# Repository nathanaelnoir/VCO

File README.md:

# AHS VCO `main_clean`

This README describes the behavior of `main_clean/main/main.ino` in musical and mathematical terms. The sketch is a three-mode Mozzi oscillator for Arduino Nano with:

- 2-operator FM mode
- chord oscillator-bank mode
- additive oscillator-bank mode

The firmware runs Mozzi in 2-pin PWM output mode with a control rate of 128 Hz. Audio generation happens in `updateAudio()`, while potentiometers, CV inputs, mode switching, oscillator frequencies, and table selections are updated in `updateControl()`.

## Inputs And Modes

The sketch reads these analog inputs:

| Name in code | Analog input | Main purpose |
| --- | ---: | --- |
| `AnalogRead0` | A0 | base pitch knob |
| `AnalogRead1` | A1 | mode-dependent parameter 1 |
| `Mode_CV` | A2 | mode CV selection |
| `AnalogRead3` | A3 | mode-dependent parameter 2 |
| `AnalogRead4` | A4 | CV for parameter 1 |
| `AnalogRead5` | A5 | CV for parameter 2 |
| `Gain_CV_*` | A6 | output level CV |
| `AnalogRead7` | A7 | V/oct input |

There are three synthesis modes:

```cpp
kModeFm       = 0
kModeChord    = 1
kModeAdditive = 2
```

The physical mode switch chooses a base ordering, and the mode CV chooses one of the three modes inside that ordering. Mathematically, the result is a discrete selector:

$$
M \in \{\mathrm{FM}, \mathrm{Chord}, \mathrm{Additive}\}
$$

where `Mode_CV` is computed by mapping the mode CV ADC value into:

$$
\mathrm{ModeCV} = \left\lfloor \mathrm{map}(A_2, 0, 1023, 0, 2) \right\rfloor
$$

The switch then permutes the three possible modes.

## Pitch Model

The sketch uses a lookup table called `voctpow`. It stores values from roughly `0` to `4.995`, indexed by the V/oct ADC input. The frequency logic repeatedly uses:

$$
f = f_\mathrm{base} \cdot 2^{V}
$$

where:

$$
V = \mathrm{voctpow}[\mathrm{ADC}]
$$

So the table is effectively a quantized exponential pitch control. If the V/oct ADC index increases by about one octave worth of table distance, the frequency doubles.

The helper:

```cpp
readVoctPow(index)
```

constrains the index to `0...1023`, then reads the floating-point value from program memory. This protects table access when chord offsets and inversion offsets are added.

## Output Level

The level CV is mapped to `0...255`:

$$
G = \mathrm{map}(A_6, 0, 1023, 0, 255)
$$

Audio samples are usually multiplied by:

$$
\frac{G}{256}
$$

Then the result is clipped to the signed 8-bit audio range:

$$
y = \mathrm{clip}(x, -128, 127)
$$

This is what `clipAudio8()` does.

## Wavetable Oscillators

The sketch uses Mozzi `Oscil` objects. Conceptually, each oscillator reads periodically through a table:

$$
x[n] = T(\phi[n])
$$

with phase:

$$
\phi[n+1] = \phi[n] + \Delta \phi
$$

where the phase increment is proportional to frequency:

$$
\Delta \phi \propto \frac{f}{f_s}
$$

Different tables give different waveforms:

| Wave enum | Table |
| --- | --- |
| `kWaveSaw` | saw |
| `kWaveSquare` | square |
| `kWaveTriangle` | triangle |
| `kWaveSine` | sine |
| `kWaveChebyshev` | Chebyshev waveshape |
| `kWaveHalfSine` | half sine |
| `kWaveSigmoid` | sigmoid waveshape |
| `kWavePhasor` | phasor |

## FM / 2-Operator Mode

FM mode uses one carrier oscillator and one modulator oscillator. In `main_clean`, both are cosine-table oscillators:

```cpp
aCarrier(COS2048_DATA)
aModulator(COS2048_DATA)
```

The base carrier frequency is computed from the pitch knob and V/oct input:

$$
f_c = (2270658 + 5000A_0) \cdot 2^V
$$

This value is a fixed-point Mozzi frequency value, not a simple Hz value. The important musical idea is:

- `A0` raises the base carrier frequency
- V/oct multiplies the frequency exponentially

The modulator frequency is derived from the carrier frequency and parameter 1:

$$
f_m \propto f_c \cdot \left(\frac{A_1}{2} + \frac{A_4}{2}\right)
$$

In code:

```cpp
mod_freq = ((carrier_freq >> 8) * (A1 / 2 + A4 / 2));
```

So parameter 1 and its CV act like a modulation-ratio or modulation-frequency control. It is not a clean integer ratio knob; it is a broad digital scaling of the carrier frequency.

The phase deviation is computed from the modulator frequency and parameter 2:

$$
D \propto f_m \cdot (1 + A_3 + A_5)
$$

In code:

```cpp
deviation = ((mod_freq >> 16) * (1 + A3 + A5));
```

The FM signal is then:

$$
y[n] = \cos\left(\phi_c[n] + D \cdot \cos(\phi_m[n])\right)
$$

scaled by the level CV:

$$
y_\mathrm{out}[n] =
\mathrm{clip}
\left(
y[n] \cdot \frac{G}{256},
-128,
127
\right)
$$

This is classic phase modulation, which is closely related to FM. The audible sidebands depend on the ratio:

$$
r = \frac{f_m}{f_c}
$$

and the modulation index/deviation:

$$
\beta \approx D
$$

For sinusoidal FM, the idealized spectrum is often described as:

$$
y(t) = \sin(2\pi f_c t + \beta \sin(2\pi f_m t))
$$

which expands into sidebands around the carrier:

$$
f = f_c \pm k f_m
$$

for integer:

$$
k = 0, 1, 2, \dots
$$

In this sketch, the scaling is fixed-point and quite aggressive, so the result is more practical/performative than mathematically normalized FM.

## Chord Mode

Chord mode creates a five-oscillator stack. Four notes come from a chord table, and the fifth oscillator repeats the root.

The chord table stores pitch offsets:

```cpp
chord_table[8][4]
```

Each row is a chord type:

| Index | Meaning |
| ---: | --- |
| 0 | major |
| 1 | major 7 |
| 2 | major add 9 |
| 3 | sus 2 |
| 4 | minor add 9 |
| 5 | minor 7 |
| 6 | minor |
| 7 | root only |

The chord selector combines the parameter 2 knob and CV:

$$
c = \mathrm{clip}
\left(
\left\lfloor \frac{A_3}{128} \right\rfloor
+
\left\lfloor \frac{A_5}{128} \right\rfloor,
0,
7
\right)
$$

The inversion selector combines parameter 1 and its CV:

$$
i = \mathrm{clip}
\left(
\left\lfloor \frac{A_1}{64} \right\rfloor
+
\left\lfloor \frac{A_4}{64} \right\rfloor,
0,
15
\right)
$$

The inversion state chooses octave shifts for the chord tones:

$$
o_1,o_2,o_3,o_4 \in \{0,1,2\}
$$

and whether the repeated root oscillator is active:

$$
r_5 \in \{0,1\}
$$

The code calls these:

```cpp
inv_aply1
inv_aply2
inv_aply3
inv_aply4
inv_aply5
```

The constant:

```cpp
kOctaveTableStep = 205
```

is the approximate table-index distance for one octave in `voctpow`. So each chord oscillator frequency is:

$$
f_j =
f_\mathrm{root}
\text{ converted through }
2^{V + \mathrm{note}_j + 205o_j}
$$

More explicitly:

$$
f_j =
f_0 \cdot
2^{
\mathrm{voctpow}
\left[
A_7 + 205o_j + n_j
\right]
}
$$

where:

- \(f_0 = A_0 / 4\)
- \(A_7\) is the V/oct ADC index
- \(o_j\) is the inversion octave offset
- \(n_j\) is the chord-table pitch offset

The fifth voice repeats the root:

$$
f_5 =
f_0 \cdot
2^{
\mathrm{voctpow}
\left[
A_7 + n_1
\right]
}
$$

but its audio is multiplied by `inv_aply5`, so it can be switched on or off:

$$
y_5[n] \cdot r_5
$$

### Chord Waveform Selection

Chord mode has selectable waveform banks. Normally parameter 1 controls inversion. But if parameter 1 is fully clockwise:

$$
A_1 \ge 1020
$$

then parameter 2 becomes a waveform selector:

$$
w = \left\lfloor \frac{A_3}{128} \right\rfloor
$$

So the 0...1023 ADC range is split into eight waveform zones.

The chord output is approximately:

$$
y[n] =
\frac{x_1[n]}{8}
+
\frac{x_2[n]}{8}
+
\frac{x_3[n]}{8}
+
\frac{x_4[n]}{8}
+
r_5\frac{x_5[n]}{8}
$$

then scaled by level:

$$
y_\mathrm{out}[n] =
\mathrm{clip}
\left(
y[n]\frac{G}{256},
-128,
127
\right)
$$

This is a parallel oscillator-bank chord. It is not additive synthesis in the Fourier sense, because the oscillators are tuned to chord intervals rather than harmonic multiples of one fundamental.

## Additive Mode

Additive mode uses eight sine oscillators:

```cpp
aSin1 ... aSin8
```

The base frequency is:

$$
f_0 = \frac{A_0}{8} \cdot 2^{\mathrm{voctpow}[A_7]}
$$

The harmonic selector is:

$$
h =
\mathrm{clip}
\left(
\left\lfloor \frac{A_3}{4} \right\rfloor
+
\left\lfloor \frac{A_5}{4} \right\rfloor,
0,
255
\right)
$$

The gain-shape selector is:

$$
g =
\mathrm{clip}
\left(
\left\lfloor \frac{A_1}{4} \right\rfloor
+
\left\lfloor \frac{A_4}{4} \right\rfloor,
0,
255
\right)
$$

The harmonic table gives integer-ish frequency multipliers:

$$
m_k(h) = \mathrm{harm\_table}[k][h]
$$

The gain table gives amplitude weights:

$$
a_k(g) = \mathrm{gain\_table}[k][g]
$$

The oscillator frequencies are:

$$
f_1 = f_0
$$

and for the other seven oscillators:

$$
f_{k+2} = f_0 \cdot m_k(h)
$$

for:

$$
k = 0,1,2,3,4,5,6
$$

The output is:

$$
y[n] =
\sum_{k=0}^{7}
\left(
\frac{a_k(g)}{1024}
\right)
\sin(2\pi f_k n / f_s)
$$

then level-scaled:

$$
y_\mathrm{out}[n] =
\mathrm{clip}
\left(
y[n]\frac{G}{256},
-128,
127
\right)
$$

### Why It Is “Kind Of Fourier” But Not Exactly

Classical additive synthesis can recreate a periodic waveform by summing harmonically related sine waves:

$$
x(t) =
\sum_{k=1}^{N}
A_k \sin(2\pi k f_0 t + \phi_k)
$$

This is close to a finite Fourier series when:

1. all partial frequencies are exact integer multiples of one fundamental,
2. amplitudes \(A_k\) represent Fourier coefficients,
3. phases \(\phi_k\) are controlled or known.

The sketch resembles this because it sums sine oscillators:

$$
y(t) =
\sum_{k=1}^{8}
A_k \sin(2\pi f_k t)
$$

However, it is not a strict Fourier reconstruction because:

- the multipliers come from `harm_table`, not from fixed \(1,2,3,4,\dots\)
- the amplitude curves come from `gain_table`, not from Fourier analysis of a target waveform
- oscillator phases are not used as explicit Fourier phase coefficients
- some multiplier combinations may create clustered, repeated, or nonstandard partial structures
- the controls are designed for musical morphing, not exact spectral reconstruction

So additive mode is better described as:

$$
\text{table-controlled partial synthesis}
$$

or:

$$
\text{a weighted sum of sine partials}
$$

rather than a mathematically exact Fourier synthesizer.

The most accurate compact description is:

$$
y(t; h,g) =
\sum_{k=1}^{8}
A_k(g)
\sin
\left(
2\pi f_0 M_k(h)t
\right)
$$

where:

- \(M_k(h)\) comes from `harm_table`
- \(A_k(g)\) comes from `gain_table`
- \(h\) controls the partial frequency structure
- \(g\) controls the partial amplitude structure

## Clipping And Scaling

All modes eventually produce an 8-bit signed audio sample. Since several oscillators are summed together, the sketch divides partials by constants such as `8` or `1024`, then applies level CV.

The final signal path is generally:

$$
y_\mathrm{digital}
=
\mathrm{clip}
\left(
\alpha \cdot
\sum_k x_k[n],
-128,
127
\right)
$$

where \(\alpha\) includes:

- per-partial scaling
- gain-table values
- level CV

This means high-gain settings can still saturate. Saturation here is not analog soft clipping; it is integer-range limiting:

$$
\mathrm{clip}(x,-128,127)
=
\begin{cases}
-128 & x < -128 \\
x & -128 \le x \le 127 \\
127 & x > 127
\end{cases}
$$

## Summary

The three modes are mathematically different.

### FM / 2-op

Core equation:

$$
y(t) = \cos\left(\phi_c + D\cos(\phi_m)\right)
$$

Musical behavior: sidebands, metallic tones, ratio/depth interaction.

### Chord

Core equation:

$$
y(t) = \sum_{j=1}^{5} x_j(t)
$$

Musical behavior: stacked chord tones from a pitch-offset table.

### Additive

Core equation:

$$
y(t) =
\sum_{k=1}^{8}
A_k(g)
\sin\left(2\pi f_0 M_k(h)t\right)
$$

Musical behavior: weighted sine partials, Fourier-like but table-shaped.

The important distinction is that chord mode sums independent musical notes, while additive mode sums partials related to one root frequency. Additive mode is Fourier-like because it is a sine sum, but it is not a true Fourier series because the frequency multipliers and amplitudes are chosen by musical lookup tables rather than derived from a target waveform.

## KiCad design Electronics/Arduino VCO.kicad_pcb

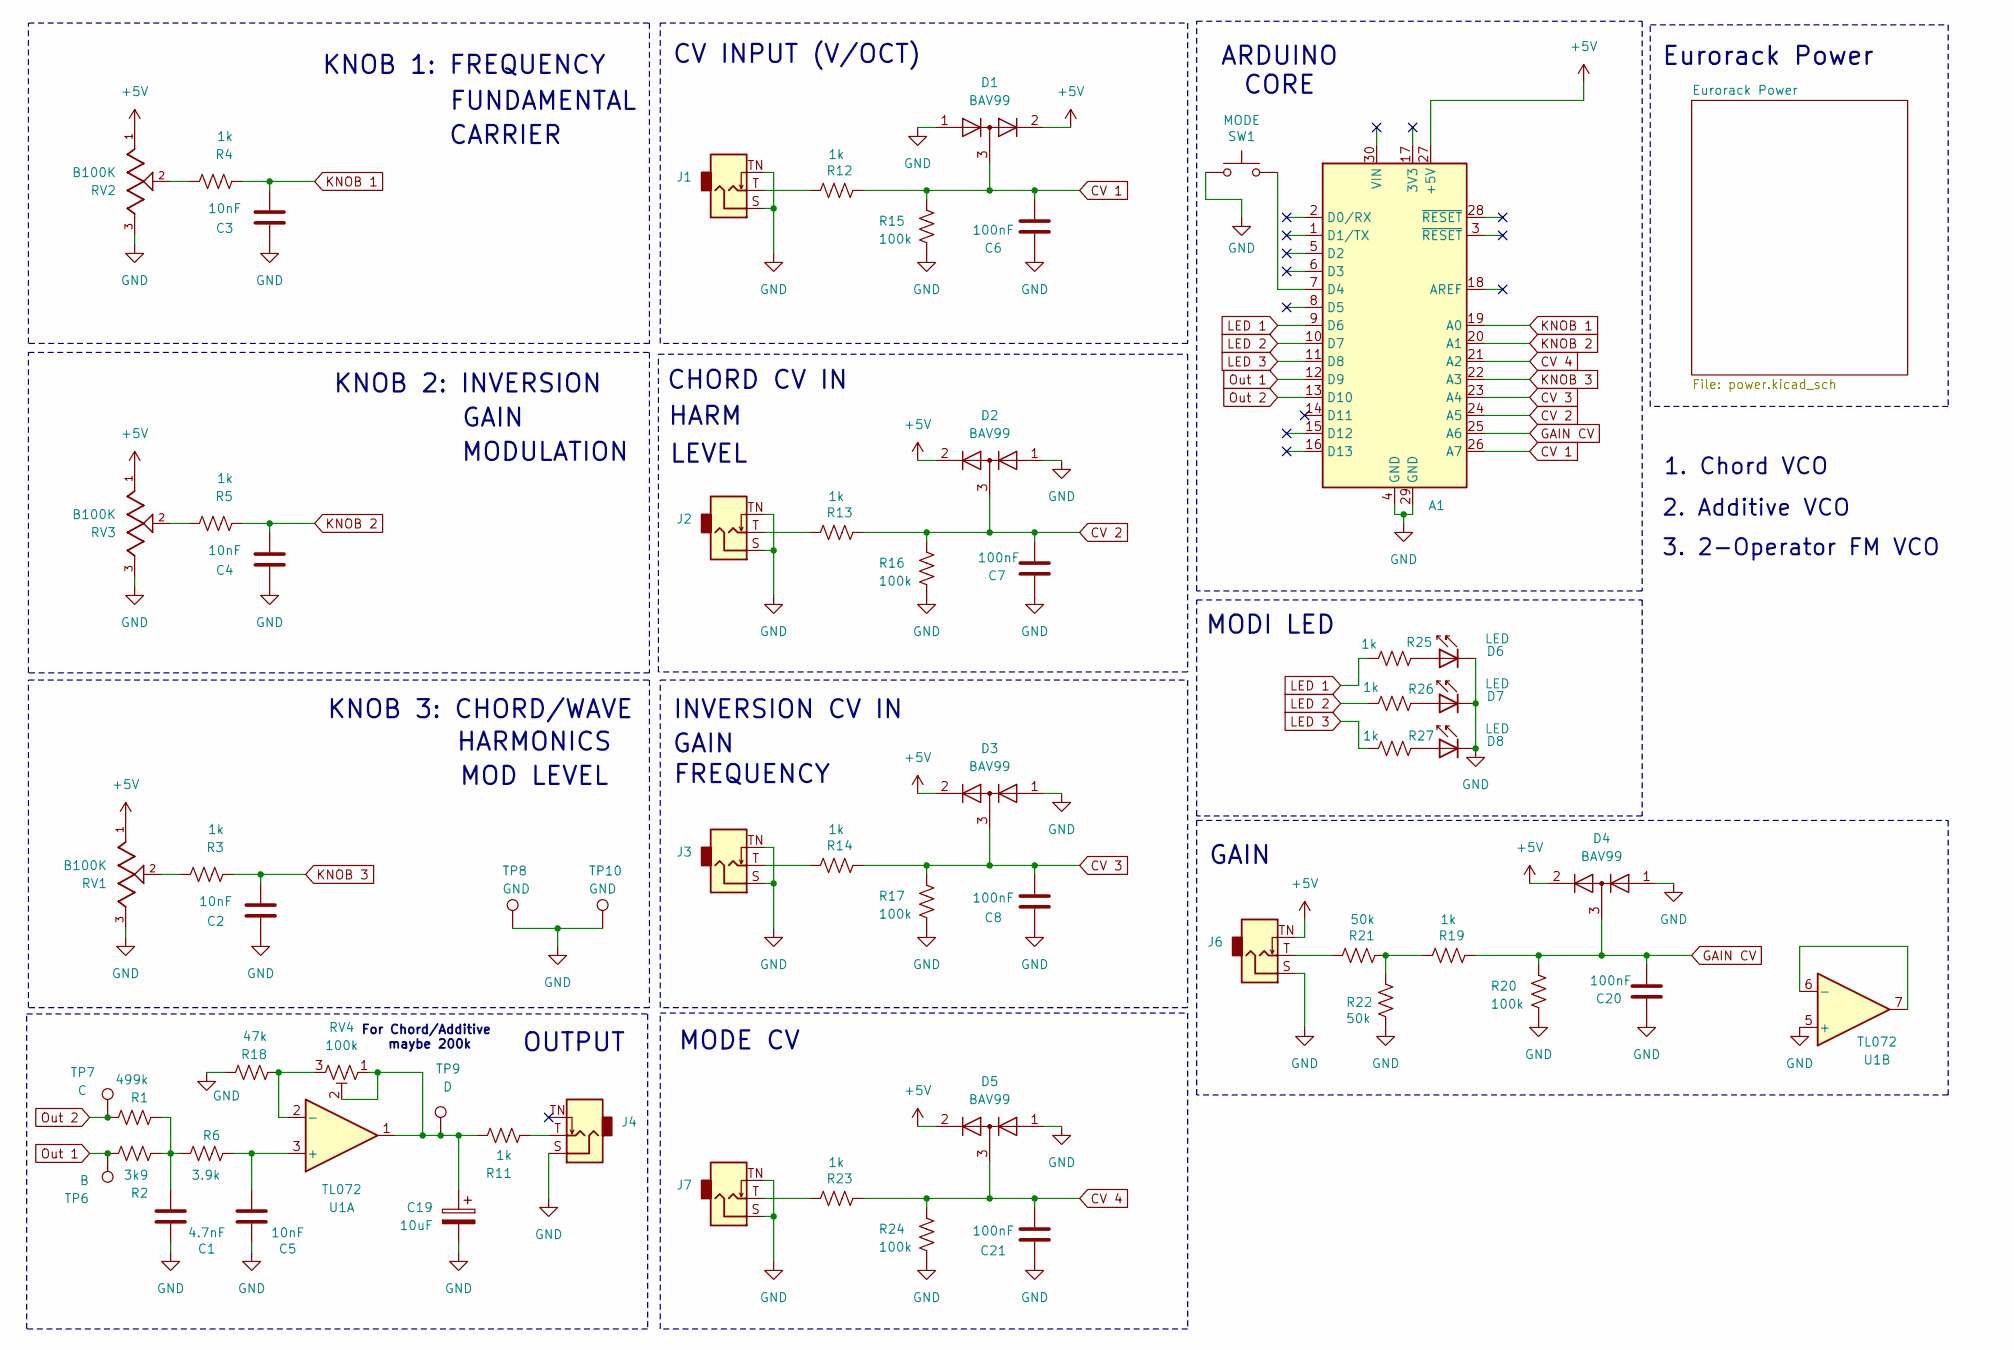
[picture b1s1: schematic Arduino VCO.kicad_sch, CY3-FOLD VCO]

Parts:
A1: Arduino_Nano_v3.x; Arduino_Nano
C1: 4.7nF; C_0805_2012Metric_Pad1.18x1.45mm_HandSolder
C2, C3, C4, C5: 10nF; C_0805_2012Metric_Pad1.18x1.45mm_HandSolder
C6, C7, C8, C20, C21: 100nF; C_0805_2012Metric_Pad1.18x1.45mm_HandSolder
C19: 10uF; CP_Elec_5x5.4
D1, D2, D3, D4, D5: BAV99; SOT-23
D6, D7, D8: LED; LED_D3.0mm_Clear
J1, J2, J3, J4, J6, J7: Jack_3.5mm_QingPu_WQP-PJ398SM_Vertical
R1: 499k; R_0805_2012Metric_Pad1.20x1.40mm_HandSolder
R2: 3k9; R_0805_2012Metric_Pad1.20x1.40mm_HandSolder
R3, R4, R5, R11, R12, R13, R14, R19, R23, R25, R26, R27: 1k; R_0805_2012Metric_Pad1.20x1.40mm_HandSolder
R6: 3.9k; R_0805_2012Metric_Pad1.20x1.40mm_HandSolder
R15, R16, R17, R20, R24: 100k; R_0805_2012Metric_Pad1.20x1.40mm_HandSolder
R18: 47k; R_0805_2012Metric_Pad1.20x1.40mm_HandSolder
R21, R22: 50k; R_0805_2012Metric_Pad1.20x1.40mm_HandSolder
RV1, RV2, RV3: B100K; Potentiometer_Alpha_RD901F_Vertical_Alt; PARTREV 10/5/23
RV4: 100k; Trimmer_Bourns_3296W_50k_THT
SW1: MODE; SW_PUSH_6mm_H13mm_1
TP6: B; TestPoint_Pad_D1.5mm
TP7: C; TestPoint_Pad_D1.5mm
TP8, TP10: GND; TestPoint_Pad_D1.5mm
TP9: D; TestPoint_Pad_D1.5mm
U1: TL072; SOIC-8_3.9x4.9mm_P1.27mm

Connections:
+5V: A1.27 (+5V), D1.2 (A), D2.2 (A), D3.2 (A), D4.2 (A), D5.2 (A), J6.TN, RV1.1, RV2.1, RV3.1; also elsewhere on the board
CV 1: A1.26 (A7), C6.2, D1.3 (K), R12.2, R15.2
CV 2: A1.24 (A5), C7.2, D2.3 (K), R13.2, R16.2
CV 3: A1.23 (A4), C8.2, D3.3 (K), R14.2, R17.2
CV 4: A1.21 (A2), C21.2, D5.3 (K), R23.2, R24.2
GAIN CV: A1.25 (A6), C20.2, D4.3 (K), R19.2, R20.2
GND: A1.4 (GND), A1.29 (GND), C1.2, C2.1, C3.1, C4.1, C5.2, C6.1, C7.1, C8.1, C19.2, C20.1, C21.1, D1.1 (K), D2.1 (K), D3.1 (K), D4.1 (K), D5.1 (K), D6.1 (K), D7.1 (K), D8.1 (K), J1.S, J1.TN, J2.S, J2.TN, J3.S, J3.TN, J4.S, J6.S, J7.S, J7.TN, R15.1, R16.1, R17.1, R18.1, R20.1, R22.1, R24.1, RV1.3, RV2.3, RV3.3, SW1.1, TP8.1 (1_1), TP10.1, U1.5 (+); also elsewhere on the board
KNOB 1: A1.19 (A0), C3.2, R4.2
KNOB 2: A1.20 (A1), C4.2, R5.2
KNOB 3: A1.22 (A3), C2.2, R3.2
LED 1: A1.9 (D6), R25.1
LED 2: A1.10 (D7), R26.1
LED 3: A1.11 (D8), R27.1
unnamed: A1.7 (D4), SW1.2
unnamed: C1.1, R1.2, R2.2, R6.1
unnamed 17: C19.1, R11.1, RV4.1, RV4.2, TP9.1, U1.1; also elsewhere on the board
unnamed: D6.2 (A), R25.2
unnamed: D7.2 (A), R26.2
unnamed: D8.2 (A), R27.2
unnamed: J1.T, R12.1
unnamed: J2.T, R13.1
unnamed: J3.T, R14.1
unnamed: J4.T, R11.2
unnamed: J6.T, R21.1
unnamed: J7.T, R23.1
unnamed: R3.1, RV1.2
unnamed: R4.1, RV2.2
unnamed: R5.1, RV3.2
unnamed: R19.1, R21.2, R22.2
unnamed: C5.1, R6.2, U1.3 (+)
unnamed: R18.2, RV4.3, U1.2 (-)
unnamed: U1.6 (-), U1.7
Out 1: A1.12 (D9), R2.1, TP6.1; also elsewhere on the board
Out 2: A1.13 (D10), R1.1, TP7.1; also elsewhere on the board

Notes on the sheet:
CHORD CV IN
HARMONICS
MODI LED
For Chord/Additive maybe 200k
FREQUENCY
CV INPUT (V/OCT)
KNOB 1: FREQUENCY
FUNDAMENTAL
KNOB 3: CHORD/WAVE
MOD LEVEL
ARDUINO CORE
2. Additive VCO
KNOB 2: INVERSION
3. 2-Operator FM VCO
Eurorack Power
GAIN
OUTPUT
1. Chord VCO
CARRIER
INVERSION CV IN
LEVEL
MODE CV
MODULATION
HARM

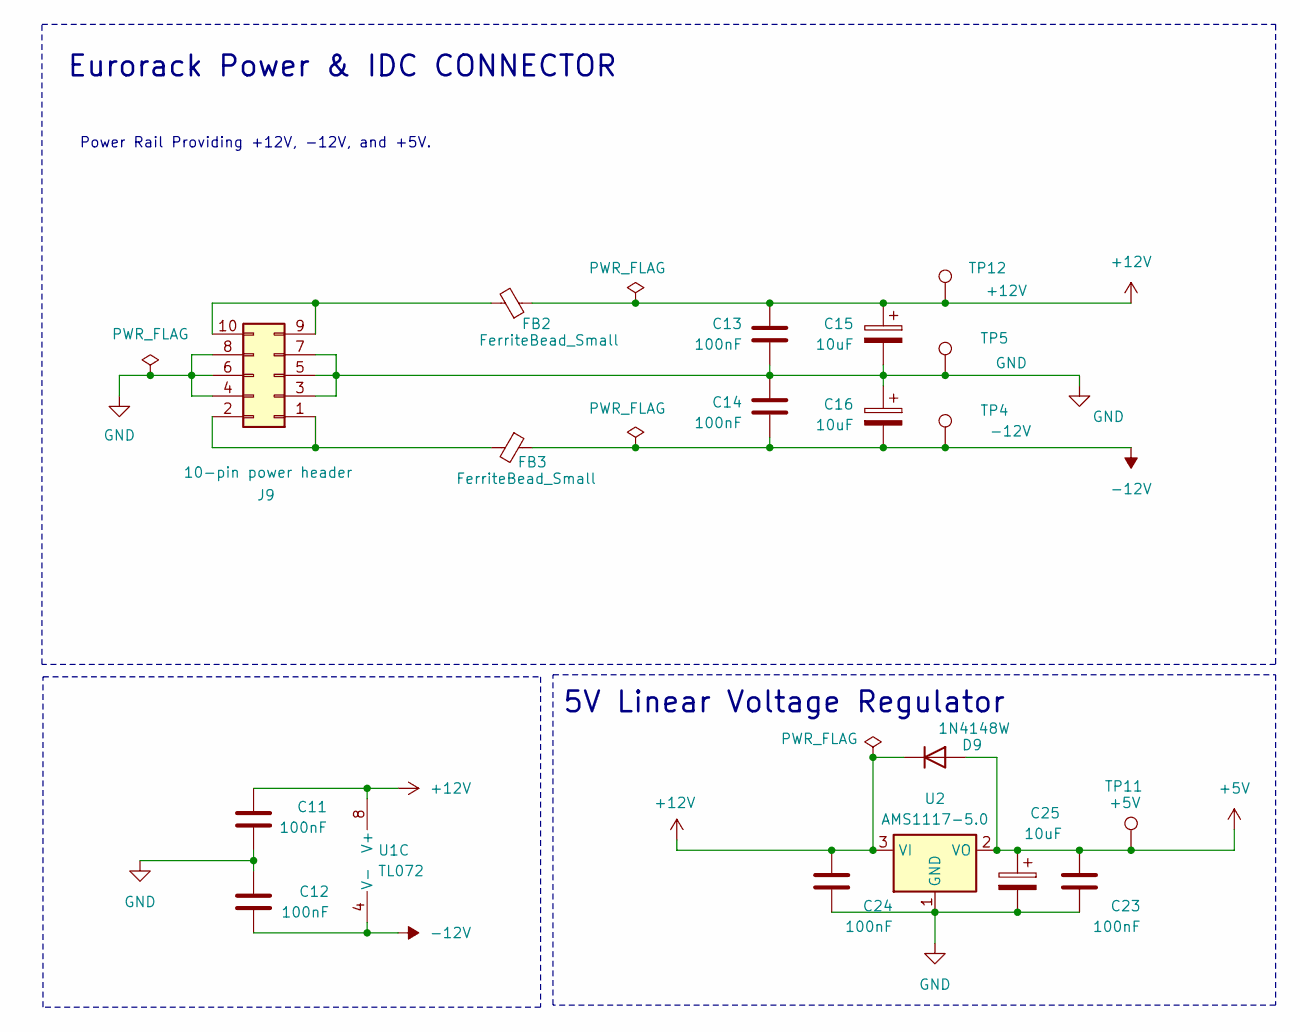
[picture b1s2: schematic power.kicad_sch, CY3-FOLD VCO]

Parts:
C11, C12, C13, C14, C23, C24: 100nF; C_0805_2012Metric_Pad1.18x1.45mm_HandSolder
C15, C16, C25: 10uF; CP_Elec_5x5.4
D9: 1N4148W; D_SOD-123
FB2, FB3: FerriteBead_Small; L_0805_2012Metric_Pad1.05x1.20mm_HandSolder
J9: 10-pin power header; IDC-Header_2x05_P2.54mm_Vertical
TP4: -12V; TestPoint_Pad_D1.5mm
TP5: GND; TestPoint_Pad_D1.5mm
TP11: +5V; TestPoint_Pad_D1.5mm
TP12: +12V; TestPoint_Pad_D1.5mm
U1: TL072; SOIC-8_3.9x4.9mm_P1.27mm
U2: AMS1117-5.0; SOT-223-3_TabPin2

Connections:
+5V: C23.1, C25.1, D9.2 (A), TP11.1, U2.2 (VO); also elsewhere on the board
+12V: C11.1, C13.1, C15.1, C24.1, D9.1 (K), FB2.1, U1.8 (V+), U2.3 (VI); also elsewhere on the board
-12V: C12.2, C14.2, C16.2, FB3.1, TP4.1 (1_1), U1.4 (V-)
GND: C11.2, C12.1, C13.2, C14.1, C15.2, C16.1, C23.2, C24.2, C25.2, J9.3, J9.4, J9.5, J9.6, J9.7, J9.8, TP5.1 (1_1), U2.1 (GND); also elsewhere on the board
unnamed: FB3.2, J9.1, J9.2
unnamed: FB2.2, J9.9, J9.10

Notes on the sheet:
Power Rail Providing +12V, -12V, and +5V.
Eurorack Power & IDC CONNECTOR
5V Linear Voltage Regulator

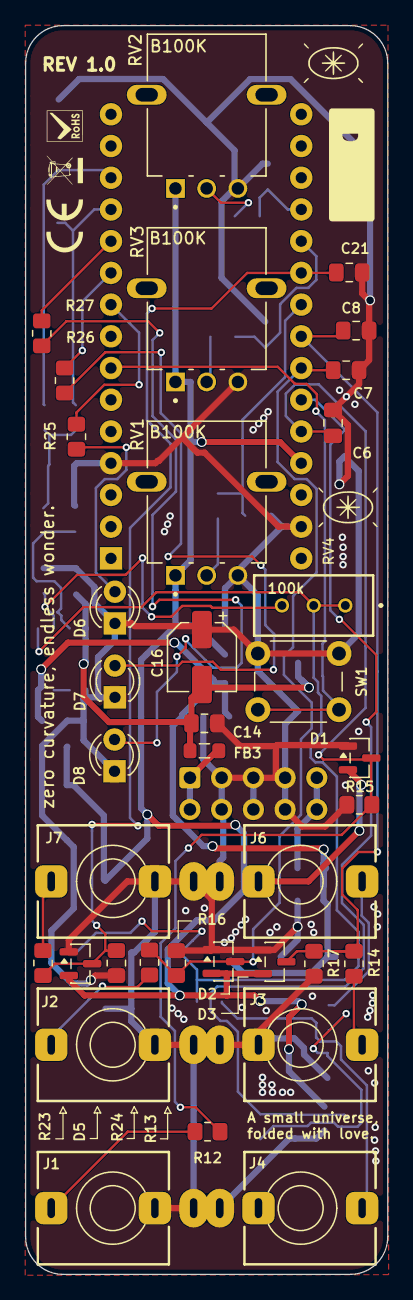
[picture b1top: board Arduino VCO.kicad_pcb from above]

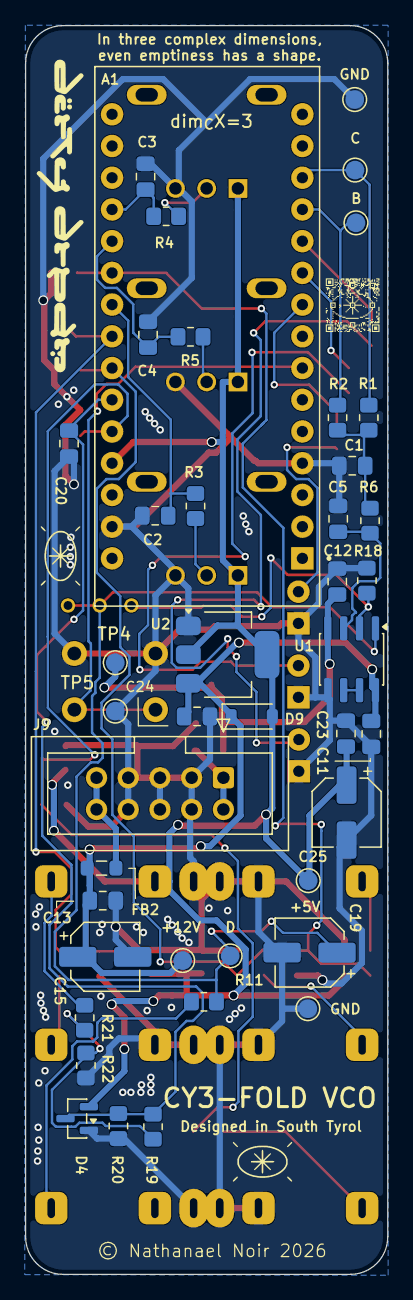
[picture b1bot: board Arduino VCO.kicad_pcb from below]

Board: 2 copper layers, 29.0 x 100.0 mm, 78 parts (42 on the bottom side), 38 nets.

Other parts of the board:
+5V: +5V; TestPoint_Pad_D1.5mm
+12V: +12V; TestPoint_Pad_D1.5mm
B: B; TestPoint_Pad_D1.5mm
C: C; TestPoint_Pad_D1.5mm
D: D; TestPoint_Pad_D1.5mm
GND: GND; TestPoint_Pad_D1.5mm

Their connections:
+5V: +5V.1 (1_1); also elsewhere on the board
+12V: +12V.1 (1_1); also elsewhere on the board
GND: GND.1 (1_1); also elsewhere on the board
unnamed 17: D.1 (1_1); also elsewhere on the board
Out 1: B.1 (1_1); also elsewhere on the board
Out 2: C.1 (1_1); also elsewhere on the board

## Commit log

2026-04-15 changing the schematic template
2026-04-15 making schematics more agnostic to arduino code
2026-04-15 renaming the global pins
2026-04-15 adding values to caps
2026-04-15 ordering the footprint nummeration
2026-04-16 changing layout
2026-04-17 deleting the plot
2026-04-18 adding a comment for potental problem
2026-04-21 optimized main_v1 reference
2026-04-21 restoring main.ino
2026-04-21 creatring folder for additive harmonic synthesis VCO
2026-04-22 adding new firmware
2026-04-22 adding further testpoints
2026-04-22 adjusting schematics layout
2026-04-23 leaving a remark of the firmwares on the schematics
2026-04-30 deleting unused files
2026-05-18 creating a 6HP PCB panel
2026-06-06 updating firmaware to mozzi v2
2026-06-06 Fix formatting in README.md and add VCO schematic files
    - Updated mathematical notation in README.md to use \mathrm{} for consistency.
    - Added new KiCad project file for VCO schematic (vco.kicad_prl).
    - Created a lock file for the KiCad project to track user session information.
2026-06-06 Refactor code structure for improved readability and maintainability
2026-06-07 Add font configuration file for KiCad CLI reports
    This commit introduces a new `fonts.conf` file to specify font directories and cache location for the KiCad CLI reports. The configuration includes standard system font directories as well as a user-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
2026-06-16 starting pcb
2026-06-17 changing tracks
2026-06-20 finishing tracks and resolving drc errors
2026-06-21 Adding Silkscreen symbols
2026-06-21 changing silkscreen letter size

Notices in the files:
Electronics/Arduino VCO.kicad_pcb:
© Dirty Dream – Nathanael Noir
© Nathanael Noir 2026
